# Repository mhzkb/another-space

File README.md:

# Another Space

14.25u ortholinear mechanical keyboard with support for up to 4 spacebars, built with PCB, plate and backplate made from FR4.

Untested 15u version is available in [1.5](1.5/).

## Hardware needed
- Pro Micro compatible controller
- 4x Brass stand-offs - 5 mm or longer
- 8x M2 screws - 4 mm
- 4-8 silicone bump-ons eg. 6x2 mm 
- 40-44 SOD-123 diodes
- 40-44 MX switches
- Keycaps

## Firmware
Firmware is available in my [Vial fork](https://github.com/mhzkb/vial-qmk/tree/vial/keyboards/mhzkb) (May need to be size-optimised for non-RP2040 controllers)

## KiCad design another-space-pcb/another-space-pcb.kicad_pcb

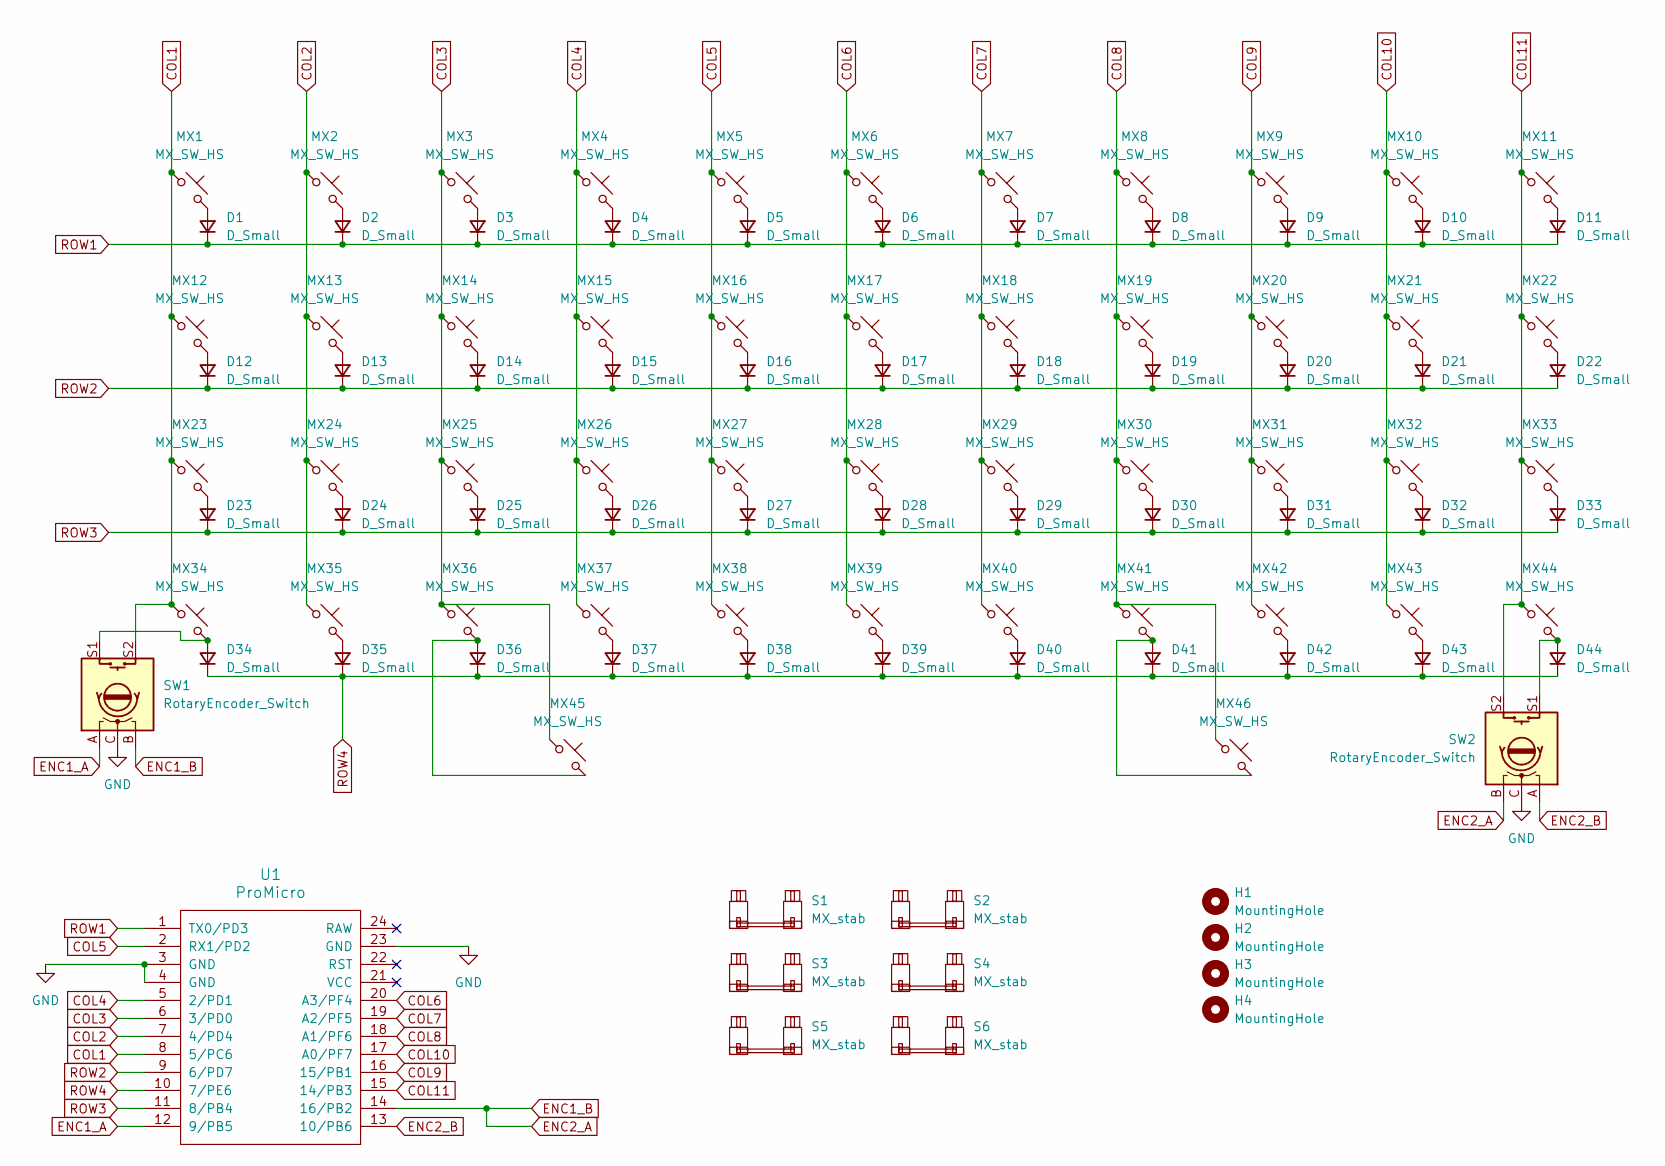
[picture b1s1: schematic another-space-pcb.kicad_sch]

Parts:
D1, D2, D3, D4, D5, D6, D7, D8, D9, D10, D11, D12, D13, D14, D15, D16, D17, D18, D19, D20, D21, D22, D23, D24, D25, D26, D27, D28, D29, D30, D31, D32, D33, D34, D35, D36, D37, D38, D39, D40, D41, D42, D43, D44: D_Small; D_SOD-123
H1, H2, H3, H4: MountingHole; MountingHole_2.2mm_M2_Pad
MX1, MX2, MX3, MX4, MX5, MX6, MX7, MX8, MX9, MX10, MX11, MX12, MX13, MX14, MX15, MX16, MX17, MX18, MX19, MX20, MX21, MX22, MX23, MX24, MX25, MX26, MX27, MX28, MX29, MX30, MX31, MX32, MX33, MX34, MX35, MX36, MX37, MX38, MX39, MX40, MX41, MX42, MX43, MX44, MX45, MX46: MX_SW_HS; SW_MX_HS_CPG151101S11_1u
S1, S2, S3, S4: MX_stab; STAB_MX_P_6.25u
S5, S6: MX_stab; STAB_MX_P_2u
SW1, SW2: RotaryEncoder_Switch; RotaryEncoder_EC11-no-legs
U1: ProMicro; ArduinoProMicro

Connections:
COL1: MX1.1, MX12.1, MX23.1, MX34.1, SW1.S2, U1.8 (5/PC6)
COL2: MX2.1, MX13.1, MX24.1, MX35.1, U1.7 (4/PD4)
COL3: MX3.1, MX14.1, MX25.1, MX36.1, MX45.1, U1.6 (3/PD0)
COL4: MX4.1, MX15.1, MX26.1, MX37.1, U1.5 (2/PD1)
COL5: MX5.1, MX16.1, MX27.1, MX38.1, U1.2 (RX1/PD2)
COL6: MX6.1, MX17.1, MX28.1, MX39.1, U1.20 (A3/PF4)
COL7: MX7.1, MX18.1, MX29.1, MX40.1, U1.19 (A2/PF5)
COL8: MX8.1, MX19.1, MX30.1, MX41.1, MX46.1, U1.18 (A1/PF6)
COL9: MX9.1, MX20.1, MX31.1, MX42.1, U1.16 (15/PB1)
COL10: MX10.1, MX21.1, MX32.1, MX43.1, U1.17 (A0/PF7)
COL11: MX11.1, MX22.1, MX33.1, MX44.1, SW2.S2, U1.15 (14/PB3)
ENC1_A: SW1.A, U1.12 (9/PB5)
ENC1_B: SW1.B, SW2.B, U1.14 (16/PB2)
ENC2_B: SW2.A, U1.13 (10/PB6)
GND: SW1.C, SW2.C, U1.3 (GND), U1.4 (GND), U1.23 (GND)
unnamed: D1.2 (A), MX1.2
unnamed: D2.2 (A), MX2.2
unnamed: D3.2 (A), MX3.2
unnamed: D4.2 (A), MX4.2
unnamed: D5.2 (A), MX5.2
unnamed: D6.2 (A), MX6.2
unnamed: D7.2 (A), MX7.2
unnamed: D8.2 (A), MX8.2
unnamed: D9.2 (A), MX9.2
unnamed: D10.2 (A), MX10.2
unnamed: D11.2 (A), MX11.2
unnamed: D12.2 (A), MX12.2
unnamed: D13.2 (A), MX13.2
unnamed: D14.2 (A), MX14.2
unnamed: D15.2 (A), MX15.2
unnamed: D16.2 (A), MX16.2
unnamed: D17.2 (A), MX17.2
unnamed: D18.2 (A), MX18.2
unnamed: D19.2 (A), MX19.2
unnamed: D20.2 (A), MX20.2
unnamed: D21.2 (A), MX21.2
unnamed: D22.2 (A), MX22.2
unnamed: D23.2 (A), MX23.2
unnamed: D24.2 (A), MX24.2
unnamed: D25.2 (A), MX25.2
unnamed: D26.2 (A), MX26.2
unnamed: D27.2 (A), MX27.2
unnamed: D28.2 (A), MX28.2
unnamed: D29.2 (A), MX29.2
unnamed: D30.2 (A), MX30.2
unnamed: D31.2 (A), MX31.2
unnamed: D32.2 (A), MX32.2
unnamed: D33.2 (A), MX33.2
unnamed: D34.2 (A), MX34.2, SW1.S1
unnamed: D35.2 (A), MX35.2
unnamed: D36.2 (A), MX36.2, MX45.2
unnamed: D37.2 (A), MX37.2
unnamed: D38.2 (A), MX38.2
unnamed: D39.2 (A), MX39.2
unnamed: D40.2 (A), MX40.2
unnamed: D41.2 (A), MX41.2, MX46.2
unnamed: D42.2 (A), MX42.2
unnamed: D43.2 (A), MX43.2
unnamed: D44.2 (A), MX44.2, SW2.S1
ROW1: D1.1 (K), D2.1 (K), D3.1 (K), D4.1 (K), D5.1 (K), D6.1 (K), D7.1 (K), D8.1 (K), D9.1 (K), D10.1 (K), D11.1 (K), U1.1 (TX0/PD3)
ROW2: D12.1 (K), D13.1 (K), D14.1 (K), D15.1 (K), D16.1 (K), D17.1 (K), D18.1 (K), D19.1 (K), D20.1 (K), D21.1 (K), D22.1 (K), U1.9 (6/PD7)
ROW3: D23.1 (K), D24.1 (K), D25.1 (K), D26.1 (K), D27.1 (K), D28.1 (K), D29.1 (K), D30.1 (K), D31.1 (K), D32.1 (K), D33.1 (K), U1.11 (8/PB4)
ROW4: D34.1 (K), D35.1 (K), D36.1 (K), D37.1 (K), D38.1 (K), D39.1 (K), D40.1 (K), D41.1 (K), D42.1 (K), D43.1 (K), D44.1 (K), U1.10 (7/PE6)

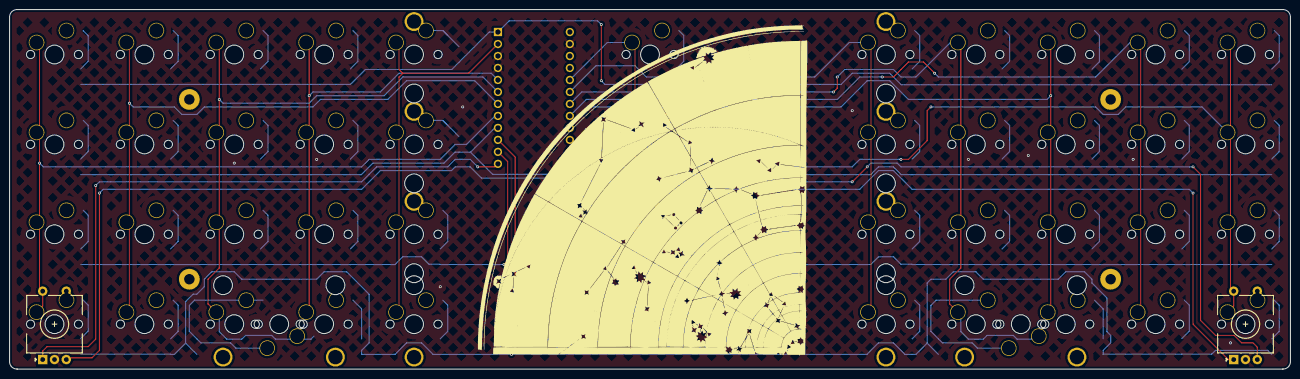
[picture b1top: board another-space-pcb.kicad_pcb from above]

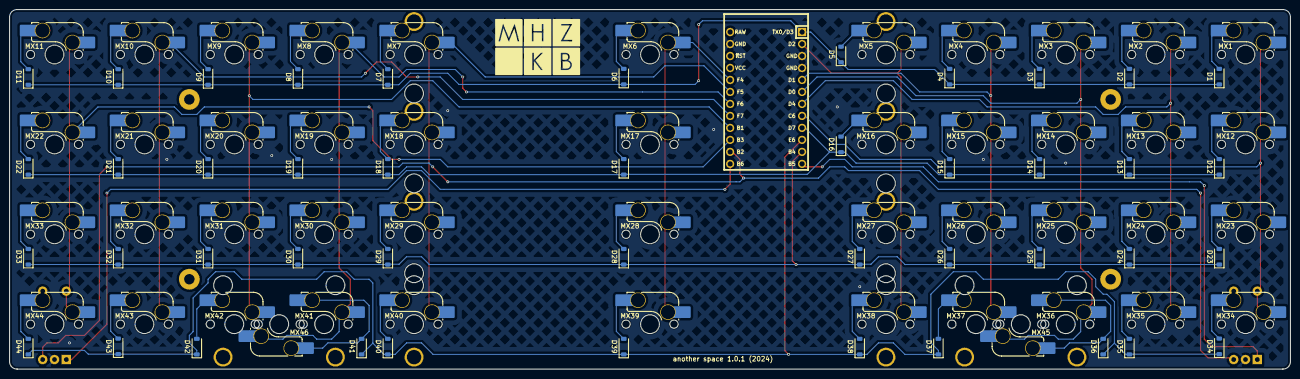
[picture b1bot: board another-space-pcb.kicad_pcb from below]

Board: 2 copper layers, 271.5 x 76.2 mm, 103 parts (90 on the bottom side), 63 nets.

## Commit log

2025-01-08 Created LICENSE
2025-01-08 Added readme
2025-10-27 Added 15u version
2026-05-04 Updated pcb silkscreen
2026-05-04 Updated 1.5 pcb silkscreen
